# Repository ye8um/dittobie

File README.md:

# Dittobie
### An Interactive Digital Desk Pet

Dittobie is an interactive digital desk pet inspired by Ditto from Pokémon. Built using the Seeed Studio XIAO ESP32-C3, Dittobie combines embedded programming, electronics, custom PCB design, pixel art, and physical interaction into a small desktop companion.

The purpose of Dittobie is to create a digital pet that feels more interactive than a character displayed on a screen. Instead of relying entirely on a computer or touchscreen, users can interact with Dittobie through physical buttons and motion-based controls.

Dittobie displays a custom pixel-art character on a small OLED screen. Users can navigate its menu, choose different actions, view pet statistics, and observe animations that give the character personality using the MPU6050, a motion sensor. The project also explores how a microcontroller, sensors, and a custom designed PCB can work together in a compact embedded system.

---

---

## Features

- **Animated Pet Display:** Displays a custom pixel-art character 48x48 on a 128×64 OLED screen.
- **Idle Animation:** Uses two key animation frames to give Dittobie more personality.
- **Motion Detection:** Uses an MPU6050 sensor to detect movement and shaking.
- **Tilt-Based Menu:** Allows the user to navigate menu options by tilting the device.
- **Interactive Actions:** Includes NAP, PLAY, EAT, and PET menu options.
- **Sleep Animation:** Displays a sleeping sprite and floating Zs while Dittobie naps.
- **Physical Controls:** Uses two buttons to access the action menu and pet statistics.
- **Custom Electronics:** Uses a custom PCB to organize and connect the components.

---

## Hardware

| Component | Purpose |
|---|---|
| Seeed Studio XIAO ESP32-C3 | Main microcontroller |
| 0.96-inch OLED display | Displays the pet and interface |
| MPU6050 | Motion and tilt detection |
| DHT11 sensor | Temperature and humidity sensing |
| 2× MX-style mechanical switches | Physical button inputs |
| Custom PCB | Connects and supports the electronics |

# Dittobie – bill of materials

<!-- Generated by Half Life from project cmuvs7tiz00j601osh18slvzp. Edits here are overwritten on the next sync. -->
<!-- Generated: 2026-10-11T21:49:35.309Z -->

> [!NOTE]
> This parts list is mirrored from [Half Life](https://halflife.hackclub.com). Editing it here will not change the platform's copy, and the next sync overwrites this file.

| Week | Tier | Parts funding |
| --- | --- | --- |
| Week 1 | Tier 1 | $30.00 |

| Part | What it's for | Qty | Unit | Total | Vendor |
| --- | --- | --- | --- | --- | --- |
| [XIAO ESP32 C3](https://www.seeedstudio.com/Seeed-XIAO-ESP32C3-p-5431.html) | Chip | 1 | $4.99 | $4.99 | [Seeed Studio](https://www.seeedstudio.com/Seeed-XIAO-ESP32C3-p-5431.html) |
| [0.96 OLED](https://www.amazon.com/dp/B0GBVWBWCR?th=1) | Screen | 1 | $5.99 | $5.99 | [Amazon](https://www.amazon.com/dp/B0GBVWBWCR?th=1) |
| [MPU6050](https://www.aliexpress.us/item/3256812536361672.html?spm=a2g0o.productlist.main.16.3691492272RBRd&utparam-url=scene%3Asearch%7Cquery_from%3Apc_back_same_best%7Cx_object_id%3A1005012722676424%7C_p_origin_prod%3A&algo_pvid=d8d7be06-5faa-483a-8edf-61a3e7c2715c&algo_exp_id=d8d7be06-5faa-483a-8edf-61a3e7c2715c&pdp_ext_f=%7B%22order%22%3A%22273%22%2C%22fromPage%22%3A%22search%22%7D&pdp_npi=6%40dis%21USD%213.86%211.09%21%21%2125.73%217.28%21%402103117b17917498346812486e1001%2112000059167286842%21sea%21US%218283334520%21ABX%211%210%21n_tag%3A-29910%3Bd%3Ac76e175c%3Bm03_new_user%3A-29895%3BpisId%3A5000000218165385&gatewayAdapt=4itemAdapt) | Gyroscope Sensor and Accelrometer | 1 | $3.86 | $3.86 | [Aliexpress](https://www.aliexpress.us/item/3256812536361672.html?spm=a2g0o.productlist.main.16.3691492272RBRd&utparam-url=scene%3Asearch%7Cquery_from%3Apc_back_same_best%7Cx_object_id%3A1005012722676424%7C_p_origin_prod%3A&algo_pvid=d8d7be06-5faa-483a-8edf-61a3e7c2715c&algo_exp_id=d8d7be06-5faa-483a-8edf-61a3e7c2715c&pdp_ext_f=%7B%22order%22%3A%22273%22%2C%22fromPage%22%3A%22search%22%7D&pdp_npi=6%40dis%21USD%213.86%211.09%21%21%2125.73%217.28%21%402103117b17917498346812486e1001%2112000059167286842%21sea%21US%218283334520%21ABX%211%210%21n_tag%3A-29910%3Bd%3Ac76e175c%3Bm03_new_user%3A-29895%3BpisId%3A5000000218165385&gatewayAdapt=4itemAdapt) |
| [DHT11](https://www.aliexpress.us/item/3256809989072342.html?spm=a2g0o.detail.similar_items.3.4aedjoGZjoGZTv&utparam-url=scene%3Aimage_search%7Cquery_from%3Aapp_pdp_sold_out%7Cx_object_id%3A1005010175387094%7C_p_origin_prod%3A&algo_pvid=899917e1-72ad-4c05-b893-4a0b1d0d16d9&algo_exp_id=899917e1-72ad-4c05-b893-4a0b1d0d16d9&pdp_ext_f=%7B%22order%22%3A%22177%22%2C%22fromPage%22%3A%22search%22%7D&pdp_npi=6%40dis%21USD%211.52%211.09%21%21%211.52%211.09%21%40210328df17917506993163760e10b9%2112000051407624945%21sea%21US%218283334520%21ABX%211%210%21n_tag%3A-29910%3Bd%3Ac76e175c%3Bm03_new_user%3A-29895%3BpisId%3A5000000218165385&gatewayAdapt=4itemAdapt) | Temperature Sensor | 1 | $1.52 | $1.52 | [Aliexpress](https://www.aliexpress.us/item/3256809989072342.html?spm=a2g0o.detail.similar_items.3.4aedjoGZjoGZTv&utparam-url=scene%3Aimage_search%7Cquery_from%3Aapp_pdp_sold_out%7Cx_object_id%3A1005010175387094%7C_p_origin_prod%3A&algo_pvid=899917e1-72ad-4c05-b893-4a0b1d0d16d9&algo_exp_id=899917e1-72ad-4c05-b893-4a0b1d0d16d9&pdp_ext_f=%7B%22order%22%3A%22177%22%2C%22fromPage%22%3A%22search%22%7D&pdp_npi=6%40dis%21USD%211.52%211.09%21%21%211.52%211.09%21%40210328df17917506993163760e10b9%2112000051407624945%21sea%21US%218283334520%21ABX%211%210%21n_tag%3A-29910%3Bd%3Ac76e175c%3Bm03_new_user%3A-29895%3BpisId%3A5000000218165385&gatewayAdapt=4itemAdapt) |
| [PCB](https://www.jlcpcb.com/) | Actual Printed Pcb | 1 | $4.00 | $4.00 | [JLCPCB](https://www.jlcpcb.com/) |
| [MX-Switches](https://www.amazon.com/YPBEW-Mechanical-Keyboard-Replacement-Accessory/dp/B0D3J3C4TC/ref=sr_1_14?crid=B8Q4AN97YO8Y&dib=eyJ2IjoiMSJ9.Xx74jyqiF6xkk52vOSkMl2HnriBWFSCKI1p97jjK7gxsfbIOwteVaAdGSG2ZUZJCUS5lpQ8clgiCSxC8TOXlrsQQhego44F6DH1H8MmM77MO7ImmtXf7d4jgGZbz49YLuSa8IpVf0i9yFqeIQj_SWcIZMk0sqiofMccD1l7UXmCuPSGtOtctKGz5GvjPpcUD0XpI_Tt6WKlz1lBjzsu8BIHpmJW1q_dSvyGX86PFjmc.IST1DuTzItsjXWGkAzthmcDbJMeDha9-U3yOYE_Kv78&dib_tag=se&keywords=mx+switches&qid=1791752464&sprefix=mx+switches%2Caps%2C162&sr=8-14) | Switches for the button | 1 | $3.99 | $3.99 | [Amazon](https://www.amazon.com/YPBEW-Mechanical-Keyboard-Replacement-Accessory/dp/B0D3J3C4TC/ref=sr_1_14?crid=B8Q4AN97YO8Y&dib=eyJ2IjoiMSJ9.Xx74jyqiF6xkk52vOSkMl2HnriBWFSCKI1p97jjK7gxsfbIOwteVaAdGSG2ZUZJCUS5lpQ8clgiCSxC8TOXlrsQQhego44F6DH1H8MmM77MO7ImmtXf7d4jgGZbz49YLuSa8IpVf0i9yFqeIQj_SWcIZMk0sqiofMccD1l7UXmCuPSGtOtctKGz5GvjPpcUD0XpI_Tt6WKlz1lBjzsu8BIHpmJW1q_dSvyGX86PFjmc.IST1DuTzItsjXWGkAzthmcDbJMeDha9-U3yOYE_Kv78&dib_tag=se&keywords=mx+switches&qid=1791752464&sprefix=mx+switches%2Caps%2C162&sr=8-14) |
| **Parts subtotal** | — | — | — | **$24.35** | — |
| **Tax & shipping** | — | — | — | **$4.99** | — |
| **Total** | — | — | — | **$29.34** | — |

$0.66 left of the tier's funding.

## KiCad PCB layout.

## Software and Tools

- Arduino IDE
- C++ and the Arduino framework
- OLED display and MPU6050 libraries
- KiCad for schematic and PCB design
- Onshape for 3D modeling, if needed

---

## Pin Configuration

The current firmware uses the following pin assignments on the XIAO ESP32-C3.

| Component | Signal | Pin |
|---|---|---|
| OLED display | SDA | D4 / GPIO6 |
| OLED display | SCL | D5 / GPIO7 |
| MPU6050 | SDA | D4 / GPIO6 |
| MPU6050 | SCL | D5 / GPIO7 |
| DHT11 | Data | D1 / GPIO3 |
| Menu button | Input | D2 / GPIO4 |
| Stats button | Input | D3 / GPIO5 |

## How It Works

Dittobie uses the XIAO ESP32-C3 to process button inputs and motion sensor data while updating the OLED display.

The OLED displays the pet's sprite and animations. The MPU6050 detects movement and tilt, allowing the user to interact with the pet. The two physical buttons provide access to the action menu and statistics screen.

The menu includes four actions:

- **NAP:** Puts Dittobie into a timed sleeping state.
- **PLAY:** Provides a play interaction.
- **EAT:** Provides a feeding interaction.
- **PET:** Provides a petting interaction.

The firmware also includes a basic idle animation to make the character feel more alive.

## Credit for the image

This is their image https://www.deviantart.com/pastel-core/art/Ditto-830029949. Check their page!

---

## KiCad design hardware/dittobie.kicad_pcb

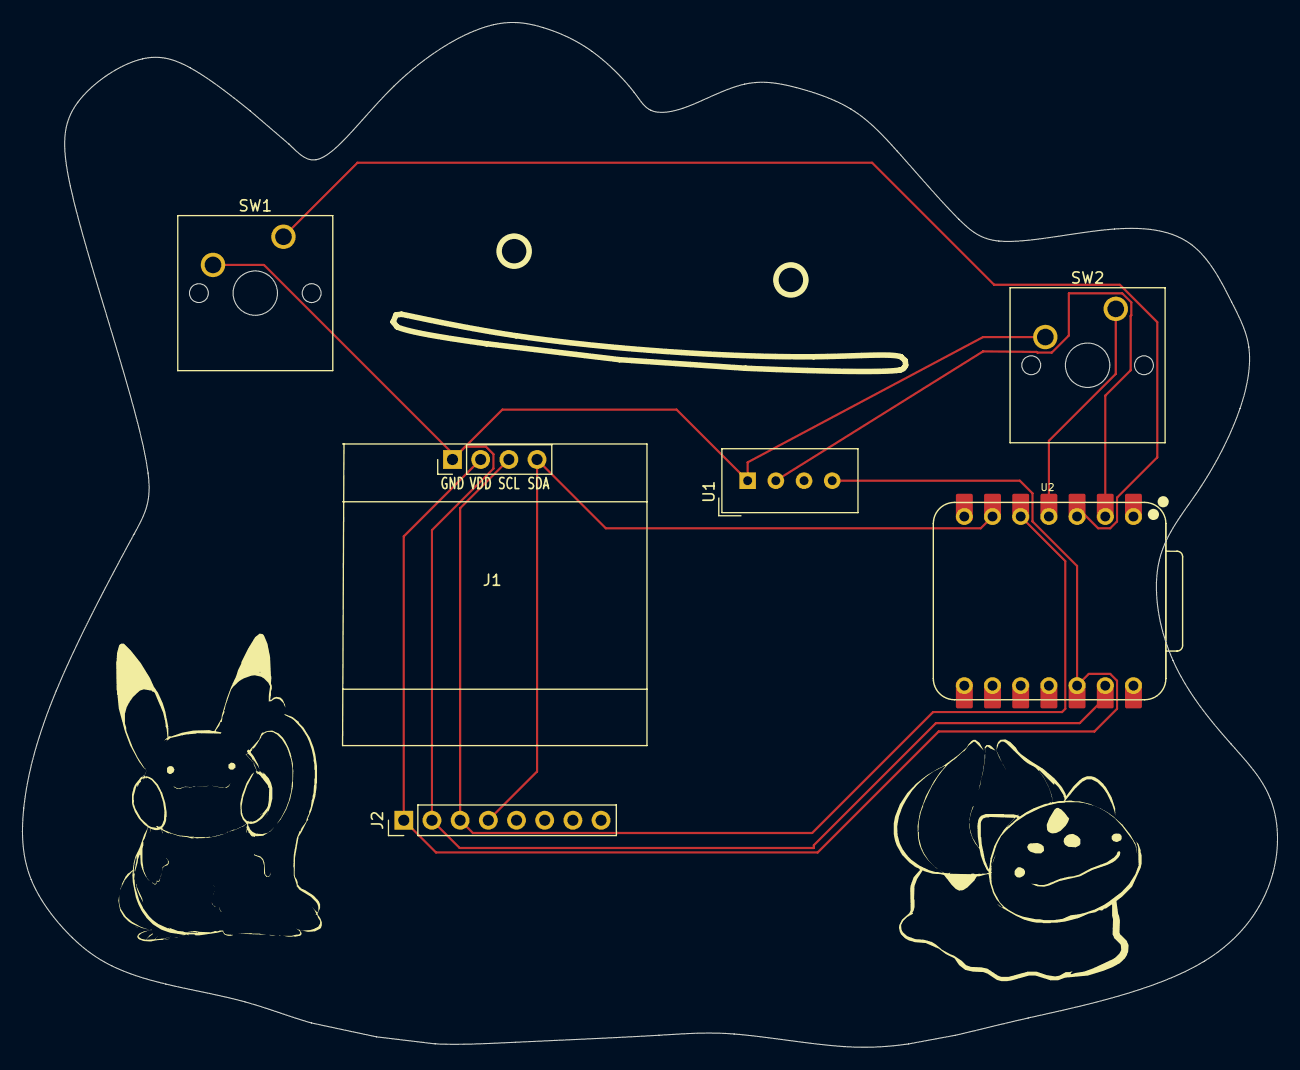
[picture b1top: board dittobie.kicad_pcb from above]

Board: 2 copper layers, 113.1 x 92.3 mm, 6 parts (0 on the bottom side), 7 nets.

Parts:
J1: Conn_01x04_Pin; Display_128x64_096_I2C
J2: Conn_01x08_Pin; PinHeader_1x08_P2.54mm_Vertical
SW1, SW2: SW_Push; SW_Cherry_MX_1.00u_PCB
U1: DHT11; Aosong_DHT11_5.5x12.0_P2.54mm
U2: XIAO-ESP32-C3-SMD; XIAO-ESP32-C6-DIP

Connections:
+3.3V: J1.2, J2.1, U1.4 (GND), U2.12 (3V3_OUT)
/DHT11 DATA: U1.2 (DATA), U2.2 (D1)
/GP103: SW2.1, U2.4 (D3)
/GPIO2: SW1.1, U2.3 (D2)
/SCL: J1.3, J2.3, U2.5 (D4)
/SDA: J1.4, J2.4, U2.6 (D5)
GND: J1.1, J2.2, SW1.2, SW2.2, U1.1 (VDD), U2.13 (GND)
